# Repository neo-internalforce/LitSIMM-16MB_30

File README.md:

# LitSIMM-16MB_30
16MB FPM 30pin SIMM enhanced with 8 LEDs

There is enough clearance under SOJ chips for the 100nF 0603 caps to fit underneath.

Not suitable for hand soldering - reflow process necessary

They work with Sound Blaster AWE, compatible PC motherboards, old Apple, MIDI keyboards, samplers, etc. Just make sure your system supports the capacity.

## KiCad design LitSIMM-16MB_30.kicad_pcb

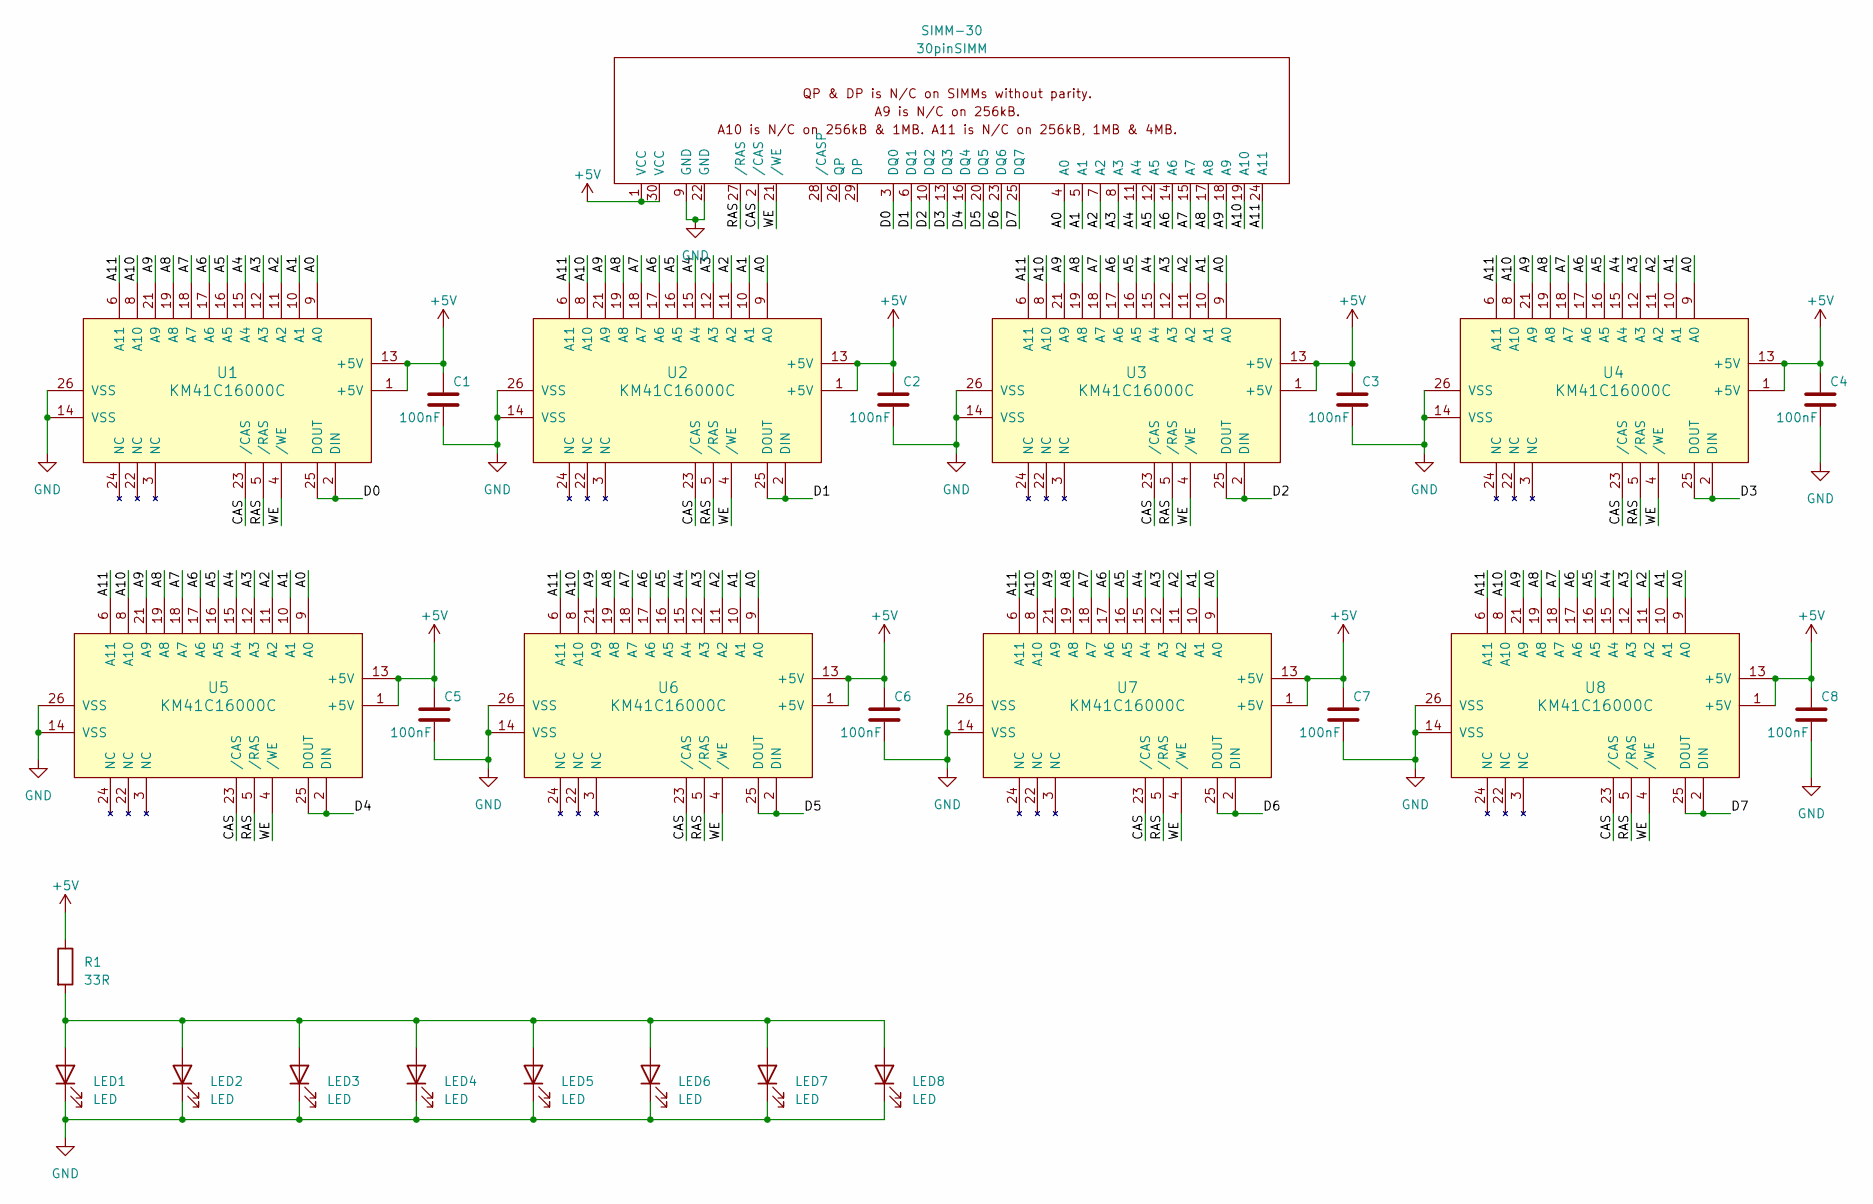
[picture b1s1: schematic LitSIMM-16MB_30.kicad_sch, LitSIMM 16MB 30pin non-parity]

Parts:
C1, C2, C3, C4, C5, C6, C7, C8: 100nF; C_0603_1608Metric
LED1, LED2, LED3, LED4, LED5, LED6, LED7, LED8: LED; LED_1206_3216Metric
R1: 33R; R_1210_3225Metric
SIMM-30: 30pinSIMM
U1, U2, U3, U4, U5, U6, U7, U8: KM41C16000C; SOJ-24

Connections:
+5V: C1.1, C2.1, C3.1, C4.1, C5.1, C6.1, C7.1, C8.1, R1.1, SIMM-30.1 (VCC), SIMM-30.30 (VCC), U1.1 (+5V), U1.13 (+5V), U2.1 (+5V), U2.13 (+5V), U3.1 (+5V), U3.13 (+5V), U4.1 (+5V), U4.13 (+5V), U5.1 (+5V), U5.13 (+5V), U6.1 (+5V), U6.13 (+5V), U7.1 (+5V), U7.13 (+5V), U8.1 (+5V), U8.13 (+5V)
/A0: SIMM-30.4 (A0), U1.9 (A0), U2.9 (A0), U3.9 (A0), U4.9 (A0), U5.9 (A0), U6.9 (A0), U7.9 (A0), U8.9 (A0)
/A1: SIMM-30.5 (A1), U1.10 (A1), U2.10 (A1), U3.10 (A1), U4.10 (A1), U5.10 (A1), U6.10 (A1), U7.10 (A1), U8.10 (A1)
/A2: SIMM-30.7 (A2), U1.11 (A2), U2.11 (A2), U3.11 (A2), U4.11 (A2), U5.11 (A2), U6.11 (A2), U7.11 (A2), U8.11 (A2)
/A3: SIMM-30.8 (A3), U1.12 (A3), U2.12 (A3), U3.12 (A3), U4.12 (A3), U5.12 (A3), U6.12 (A3), U7.12 (A3), U8.12 (A3)
/A4: SIMM-30.11 (A4), U1.15 (A4), U2.15 (A4), U3.15 (A4), U4.15 (A4), U5.15 (A4), U6.15 (A4), U7.15 (A4), U8.15 (A4)
/A5: SIMM-30.12 (A5), U1.16 (A5), U2.16 (A5), U3.16 (A5), U4.16 (A5), U5.16 (A5), U6.16 (A5), U7.16 (A5), U8.16 (A5)
/A6: SIMM-30.14 (A6), U1.17 (A6), U2.17 (A6), U3.17 (A6), U4.17 (A6), U5.17 (A6), U6.17 (A6), U7.17 (A6), U8.17 (A6)
/A7: SIMM-30.15 (A7), U1.18 (A7), U2.18 (A7), U3.18 (A7), U4.18 (A7), U5.18 (A7), U6.18 (A7), U7.18 (A7), U8.18 (A7)
/A8: SIMM-30.17 (A8), U1.19 (A8), U2.19 (A8), U3.19 (A8), U4.19 (A8), U5.19 (A8), U6.19 (A8), U7.19 (A8), U8.19 (A8)
/A9: SIMM-30.18 (A9), U1.21 (A9), U2.21 (A9), U3.21 (A9), U4.21 (A9), U5.21 (A9), U6.21 (A9), U7.21 (A9), U8.21 (A9)
/A10: SIMM-30.19 (A10), U1.8 (A10), U2.8 (A10), U3.8 (A10), U4.8 (A10), U5.8 (A10), U6.8 (A10), U7.8 (A10), U8.8 (A10)
/A11: SIMM-30.24 (A11), U1.6 (A11), U2.6 (A11), U3.6 (A11), U4.6 (A11), U5.6 (A11), U6.6 (A11), U7.6 (A11), U8.6 (A11)
/CAS: SIMM-30.2 (/CAS), U1.23 (/CAS), U2.23 (/CAS), U3.23 (/CAS), U4.23 (/CAS), U5.23 (/CAS), U6.23 (/CAS), U7.23 (/CAS), U8.23 (/CAS)
/D0: SIMM-30.3 (DQ0), U1.2 (DIN), U1.25 (DOUT)
/D1: SIMM-30.6 (DQ1), U2.2 (DIN), U2.25 (DOUT)
/D2: SIMM-30.10 (DQ2), U3.2 (DIN), U3.25 (DOUT)
/D3: SIMM-30.13 (DQ3), U4.2 (DIN), U4.25 (DOUT)
/D4: SIMM-30.16 (DQ4), U5.2 (DIN), U5.25 (DOUT)
/D5: SIMM-30.20 (DQ5), U6.2 (DIN), U6.25 (DOUT)
/D6: SIMM-30.23 (DQ6), U7.2 (DIN), U7.25 (DOUT)
/D7: SIMM-30.25 (DQ7), U8.2 (DIN), U8.25 (DOUT)
/RAS: SIMM-30.27 (/RAS), U1.5 (/RAS), U2.5 (/RAS), U3.5 (/RAS), U4.5 (/RAS), U5.5 (/RAS), U6.5 (/RAS), U7.5 (/RAS), U8.5 (/RAS)
/WE: SIMM-30.21 (/WE), U1.4 (/WE), U2.4 (/WE), U3.4 (/WE), U4.4 (/WE), U5.4 (/WE), U6.4 (/WE), U7.4 (/WE), U8.4 (/WE)
GND: C1.2, C2.2, C3.2, C4.2, C5.2, C6.2, C7.2, C8.2, LED1.1 (K), LED2.1 (K), LED3.1 (K), LED4.1 (K), LED5.1 (K), LED6.1 (K), LED7.1 (K), LED8.1 (K), SIMM-30.9 (GND), SIMM-30.22 (GND), U1.14 (VSS), U1.26 (VSS), U2.14 (VSS), U2.26 (VSS), U3.14 (VSS), U3.26 (VSS), U4.14 (VSS), U4.26 (VSS), U5.14 (VSS), U5.26 (VSS), U6.14 (VSS), U6.26 (VSS), U7.14 (VSS), U7.26 (VSS), U8.14 (VSS), U8.26 (VSS)
unnamed: LED1.2 (A), LED2.2 (A), LED3.2 (A), LED4.2 (A), LED5.2 (A), LED6.2 (A), LED7.2 (A), LED8.2 (A), R1.2

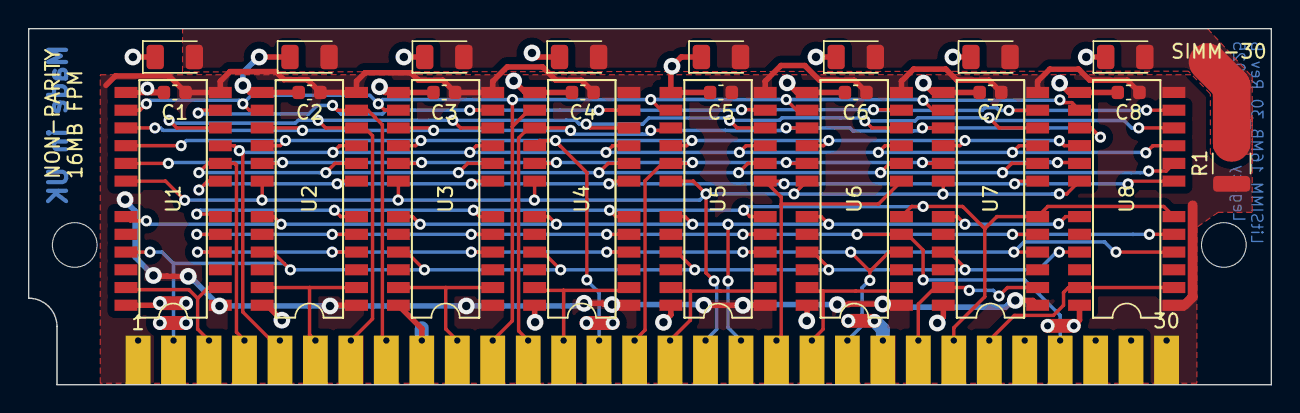
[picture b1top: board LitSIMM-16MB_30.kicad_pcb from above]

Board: 2 copper layers, 89.0 x 25.5 mm, 26 parts (0 on the bottom side), 26 nets.
